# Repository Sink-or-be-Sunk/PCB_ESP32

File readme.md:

# Sink or be Sunk Hardware

This project contains the KiCAD PCB and auxiliary hardware needed for physical gameplay.

## Helpful Notes

### Nested Sheets

In KiCAD you can use a neat feature to split your project into multiple files. This not only helps to reduce cluter on one single diagram, it also allows for reuse of a common schematic element.

For this project specifically, the Grid.sch file can be reused for both the top (attack) grid and the bottom (ship positioning) grid.

`Hierarchical Labels` - KiCAD allows you to place a label on a nested sheet that can be viewed by the parenet sheet. Ex: you place a label on the STM32 Sheet and you can connect to it from the Main Layout schematic.

- Locate the `Hierarchical Labels` button on the right hand toolbar in kicad to place a label in a child sheet.
  - See section A4 of the STM32 Sheet
- Navigate back to the parent sheet and right click on the child sheet where you jused added the label
- Select the `import sheet pins` option
  - NOTE that you will have to do this for every new pin that you add to the child sheet, kinda repetative if you have a bunch of heirarchical labels...

`ESP32 Reference Design` - Adafruit produced a reference/dev board for the ESP32. They have great documentation on the device and are generous enough to include images of their schematic. This is a good place to start for our design. See the [Adafruit Website](https://learn.adafruit.com/adafruit-huzzah32-esp32-feather/downloads) for details.

#### PCB Updates to PCB_ESP32

I added a new branch with a new file "Main", containing all updated symbol and footprint libraries. There appears to be an issue between KiCad's footprint libraries in Version 4 and 5.0+. I believe I resolved this issue, let me know if you're still missing access to certain footprints. 

Other than that, I think this is a start. One great thing about our Main PCB is that the dimensions on it are much more flexible than the Row PCBs. If we need more room, we can make the board longer (wider will start to run into the grid). 

Some things to think about:
- USB to Serial: Where is the most convenient place for the plug? 
- What are the repercussions of placing the speaker next to the motor? 
- Where on the exterior of the board should the speaker knob/reset button go, without being bumped or in the way?

There's plenty of work left, but this is the start!

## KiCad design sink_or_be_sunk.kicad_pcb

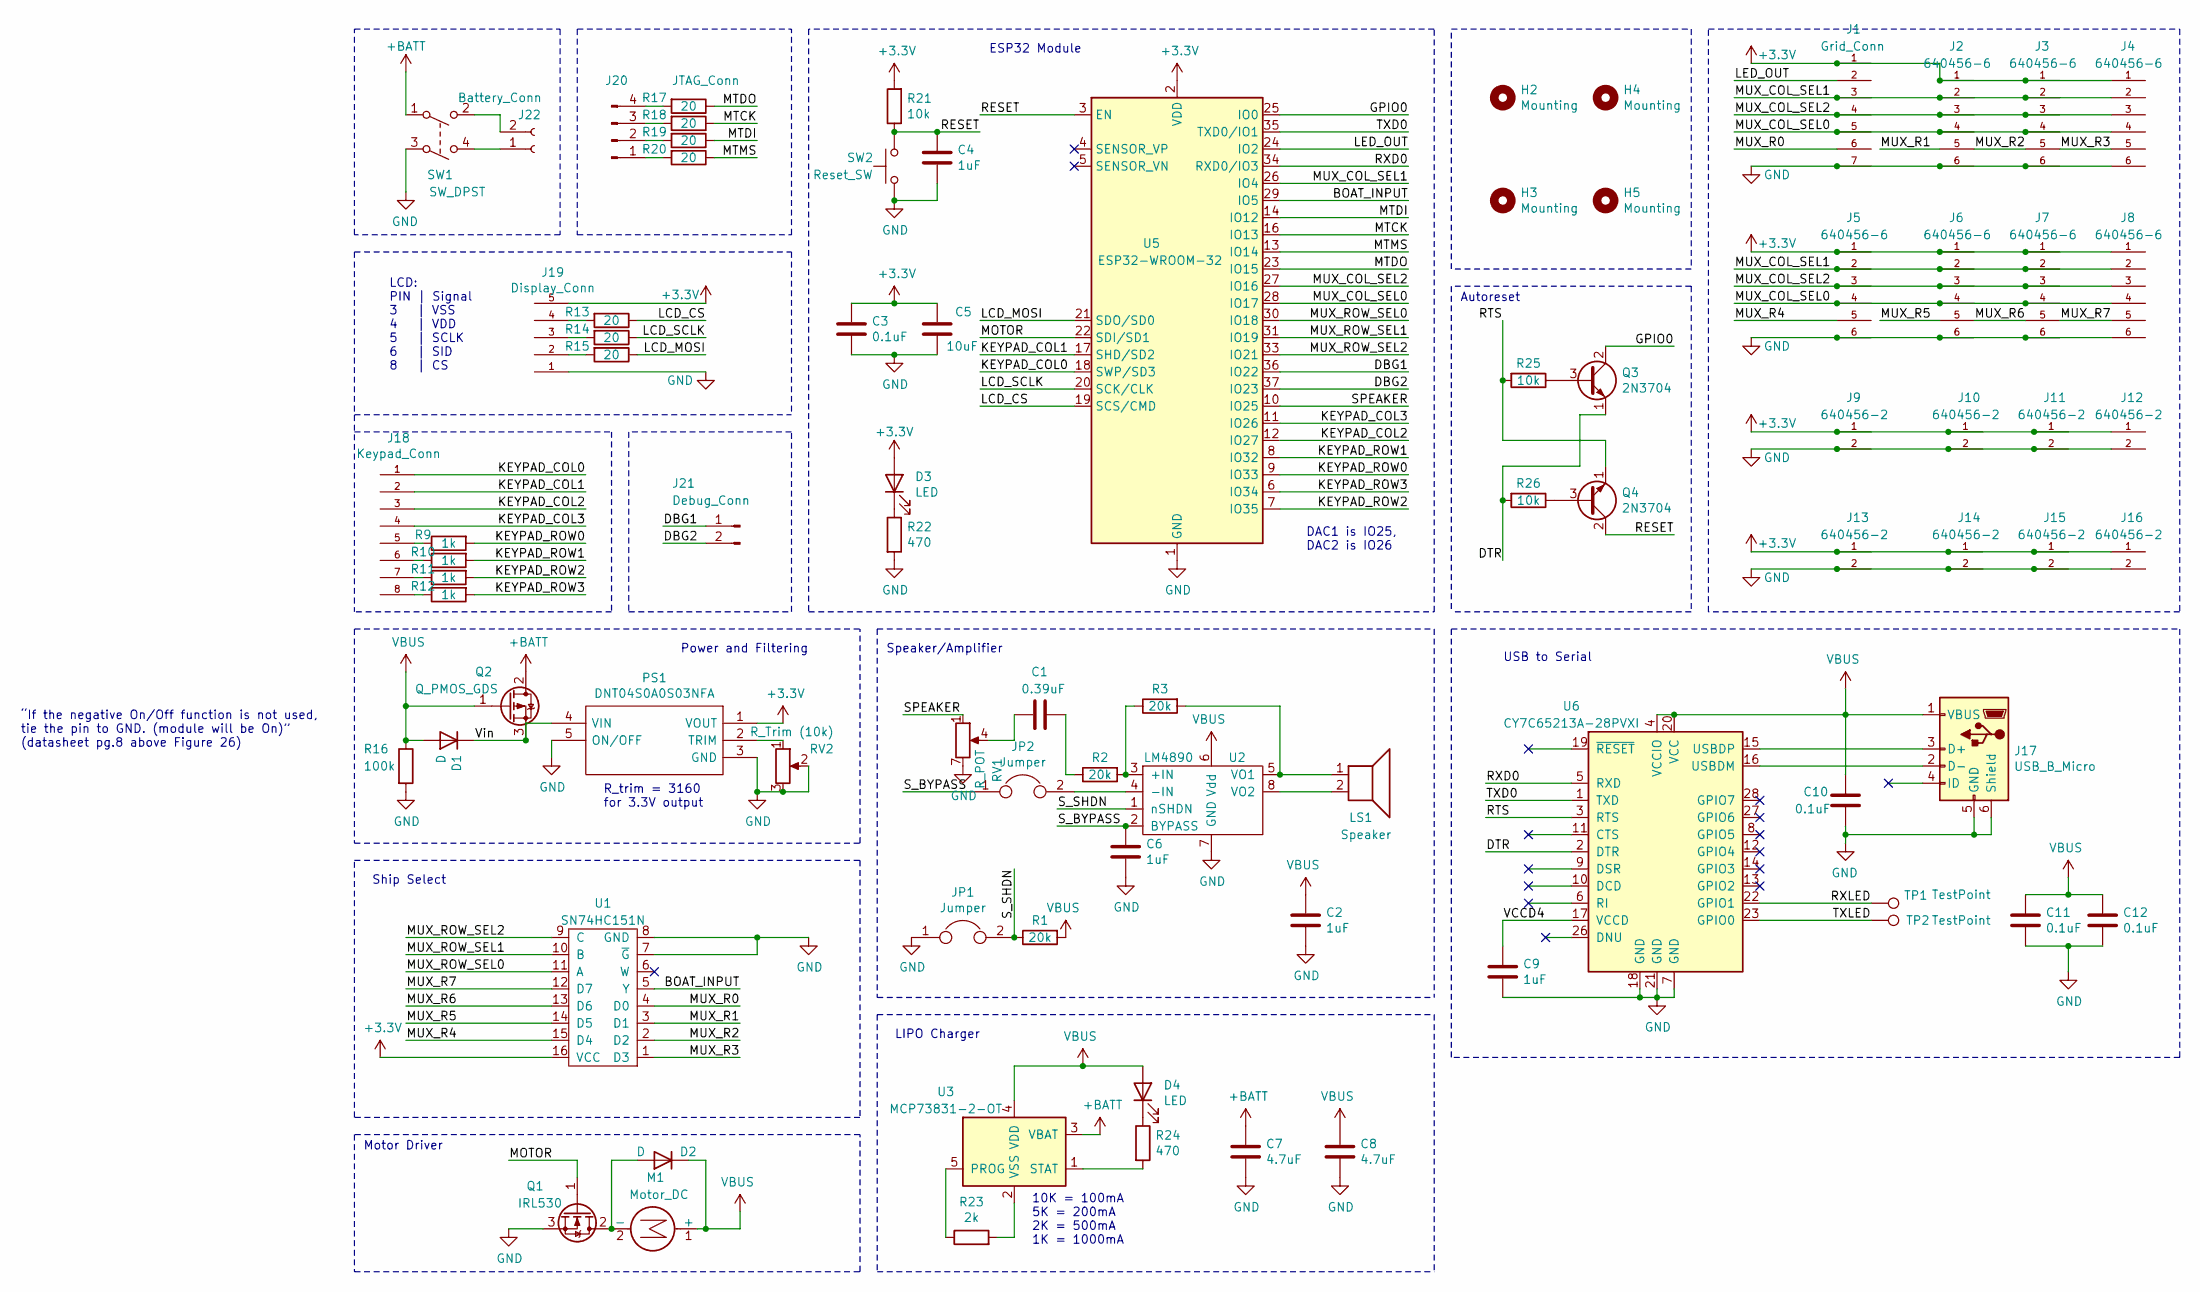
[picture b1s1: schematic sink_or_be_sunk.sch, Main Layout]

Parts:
C1: 0.39uF; C_0805_2012Metric_Pad1.18x1.45mm_HandSolder
C2, C4, C6: 1uF; C_0805_2012Metric_Pad1.18x1.45mm_HandSolder
C3, C10, C11, C12: 0.1uF; C_0805_2012Metric_Pad1.15x1.40mm_HandSolder
C5: 10uF; CP_Radial_D5.0mm_P2.50mm
C7, C8: 4.7uF; CP_Radial_D5.0mm_P2.50mm
C9: 1uF; C_0805_2012Metric_Pad1.15x1.40mm_HandSolder
D1, D2: D; D_A-405_P7.62mm_Horizontal
D3, D4: LED; LED_D3.0mm
H2, H3, H4, H5: Mounting; MountingHole_3.2mm_M3
J1: Grid_Conn; TE_640456-7
J2, J3, J4, J5, J6, J7, J8: 640456-6; TE_640456-6
J9, J10, J11, J12, J13, J14, J15, J16: 640456-2; TE_640456-2
J17: USB_B_Micro; USB_Micro_B_Female_Vert_1051330001
J18: Keypad_Conn; TE_640456-8
J19: Display_Conn; TE_640456-5
J20: JTAG_Conn; PinHeader_1x04_P2.54mm_Vertical
J21: Debug_Conn; PinHeader_1x02_P2.54mm_Vertical
J22: Battery_Conn; JST_PH_S2B-PH-K_1x02_P2.00mm_Horizontal
JP1, JP2: Jumper; PinHeader_1x02_P2.54mm_Vertical
LS1: Speaker; TE_640456-2
M1: Motor_DC; TE_640456-2
PS1: DNT04S0A0S03NFA; Mouser Part Number 108-DNT04S0A0S03NFA
Q1: IRL530; TO-220-3_Vertical
Q2: Q_PMOS_GDS; TO-251-3-1EP_Horizontal_TabDown
Q3, Q4: 2N3704; TO-92
R1, R2, R3: 20k; R_0805_2012Metric_Pad1.20x1.40mm_HandSolder
R9, R10, R11: 1k; R_0805_2012Metric_Pad1.20x1.40mm_HandSolder
R12: 1k; R_0805_2012Metric_Pad1.15x1.40mm_HandSolder
R13, R14, R15, R17, R18, R19, R20: 20; R_0805_2012Metric_Pad1.20x1.40mm_HandSolder
R16: 100k; R_0805_2012Metric_Pad1.15x1.40mm_HandSolder
R21, R25, R26: 10k; R_0805_2012Metric_Pad1.20x1.40mm_HandSolder
R22: 470; R_0805_2012Metric_Pad1.20x1.40mm_HandSolder
R23: 2k; R_0805_2012Metric_Pad1.15x1.40mm_HandSolder
R24: 470; R_0805_2012Metric_Pad1.15x1.40mm_HandSolder
RV1: R_POT; PinHeader_1x07_P2.54mm_Vertical
RV2: R_Trim (10k); Potentiometer_Bourns_3266Y_Vertical
SW1: SW_DPST; PinHeader_1x04_P2.54mm_Vertical
SW2: Reset_SW; PinHeader_1x02_P2.54mm_Vertical
TP1, TP2: TestPoint; TestPoint_Plated_Hole_D2.0mm
U1: SN74HC151N; DIP-16_W10.16mm
U2: LM4890; TSSOP-8_3x3mm_P0.65mm
U3: MCP73831-2-OT; SOT-23-5
U5: ESP32-WROOM-32
U6: CY7C65213A-28PVXI; SSOP-28_5.3x10.2mm_P0.65mm

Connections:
+3V3: C3.1, C5.1, D3.2 (A), J1.1, J2.1, J3.1, J4.1, J5.1, J6.1, J7.1, J8.1, J9.1, J10.1, J11.1, J12.1, J13.1, J14.1, J15.1, J16.1, J19.5, PS1.1 (VOUT), R21.2, U1.16 (VCC), U5.2 (VDD)
+BATT: C7.1, Q2.2 (D), SW1.1, U3.3 (VBAT)
/BOAT_INPUT: U1.5 (Y), U5.29 (IO5)
/DBG1: J21.1, U5.36 (IO22)
/DBG2: J21.2, U5.37 (IO23)
/DTR: Q3.1 (E), R26.2, U6.2 (DTR)
/GPIO0: Q3.2 (C), U5.25 (IO0)
/KEYPAD_COL0: J18.1, U5.18 (SWP/SD3)
/KEYPAD_COL1: J18.2, U5.17 (SHD/SD2)
/KEYPAD_COL2: J18.3, U5.12 (IO27)
/KEYPAD_COL3: J18.4, U5.11 (IO26)
/KEYPAD_ROW0: R9.2, U5.9 (IO33)
/KEYPAD_ROW1: R10.2, U5.8 (IO32)
/KEYPAD_ROW2: R11.2, U5.7 (IO35)
/KEYPAD_ROW3: R12.2, U5.6 (IO34)
/LCD_CS: R13.1, U5.19 (SCS/CMD)
/LCD_MOSI: R15.1, U5.21 (SDO/SD0)
/LCD_SCLK: R14.1, U5.20 (SCK/CLK)
/LED_OUT: J1.2, U5.24 (IO2)
/MOTOR: Q1.1 (G), U5.22 (SDI/SD1)
/MTCK: R18.1, U5.16 (IO13)
/MTDI: R19.1, U5.14 (IO12)
/MTDO: R17.1, U5.23 (IO15)
/MTMS: R20.1, U5.13 (IO14)
/MUX_COL_SEL0: J1.5, J2.4, J3.4, J4.4, J5.4, J6.4, J7.4, J8.4, U5.28 (IO17)
/MUX_COL_SEL1: J1.3, J2.2, J3.2, J4.2, J5.2, J6.2, J7.2, J8.2, U5.26 (IO4)
/MUX_COL_SEL2: J1.4, J2.3, J3.3, J4.3, J5.3, J6.3, J7.3, J8.3, U5.27 (IO16)
/MUX_R0: J1.6, U1.4 (D0)
/MUX_R1: J2.5, U1.3 (D1)
/MUX_R2: J3.5, U1.2 (D2)
/MUX_R3: J4.5, U1.1 (D3)
/MUX_R4: J5.5, U1.15 (D4)
/MUX_R5: J6.5, U1.14 (D5)
/MUX_R6: J7.5, U1.13 (D6)
/MUX_R7: J8.5, U1.12 (D7)
/MUX_ROW_SEL0: U1.11 (A), U5.30 (IO18)
/MUX_ROW_SEL1: U1.10 (B), U5.31 (IO19)
/MUX_ROW_SEL2: U1.9 (C), U5.33 (IO21)
/RESET: C4.1, Q4.2 (C), R21.1, SW2.2, U5.3 (EN)
/RTS: Q4.1 (E), R25.2, U6.3 (RTS)
/RXD0: U5.34 (RXD0/IO3), U6.5 (RXD)
/RXLED: TP1.1, U6.22 (GPIO1)
/SPEAKER: RV1.1, U5.10 (IO25)
/S_BYPASS: C6.1, JP2.1, U2.2 (BYPASS)
/S_SHDN: JP1.2, R1.1, U2.1 (nSHDN)
/TXD0: U5.35 (TXD0/IO1), U6.1 (TXD)
/TXLED: TP2.1, U6.23 (GPIO0)
/VCCD4: C9.1, U6.17 (VCCD)
/Vin: D1.1 (K), PS1.4 (VIN), Q2.3 (S)
GND: C2.2, C3.2, C4.2, C5.2, C6.2, C7.2, C8.2, C9.2, C10.2, C11.2, C12.2, J1.7, J2.6, J3.6, J4.6, J5.6, J6.6, J7.6, J8.6, J9.2, J10.2, J11.2, J12.2, J13.2, J14.2, J15.2, J16.2, J17.5 (GND), J17.6 (Shield), J19.1, JP1.1, PS1.3 (GND), PS1.5 (ON/OFF), Q1.3 (S), R16.2, R22.2, RV1.7, RV2.2, RV2.3, SW1.3, SW2.1, U1.7 (~G), U1.8 (GND), U2.7 (GND), U5.1 (GND), U5.15 (GND), U5.38 (GND), U5.39 (GND), U6.7 (GND), U6.18 (GND), U6.21 (GND)
unnamed: C1.1, RV1.4
unnamed: C1.2, R2.1
unnamed: D2.2 (A), M1.2 (-), Q1.2 (D)
unnamed: D3.1 (K), R22.1
unnamed: D4.1 (K), R24.1
unnamed: J17.2 (D-), U6.16 (USBDM)
unnamed: J17.3 (D+), U6.15 (USBDP)
unnamed: J18.5, R9.1
unnamed: J18.6, R10.1
unnamed: J18.7, R11.1
unnamed: J18.8, R12.1
unnamed: J19.2, R15.2
unnamed: J19.3, R14.2
unnamed: J19.4, R13.2
unnamed: J20.1, R20.2
unnamed: J20.2, R19.2
unnamed: J20.3, R18.2
unnamed: J20.4, R17.2
unnamed: J22.1, SW1.4
unnamed: J22.2, SW1.2
unnamed: JP2.2, U2.4 (-IN)
unnamed: LS1.1, R3.2, U2.5 (VO1)
unnamed: LS1.2, U2.8 (VO2)
unnamed: PS1.2 (TRIM), RV2.1
unnamed: Q3.3 (B), R25.1
unnamed: Q4.3 (B), R26.1
unnamed: R2.2, R3.1, U2.3 (+IN)
unnamed: R23.1, U3.5 (PROG)
unnamed: R23.2, U3.2 (VSS)
unnamed: R24.2, U3.1 (STAT)
VBUS: C2.1, C8.1, C10.1, C11.1, C12.1, D1.2 (A), D2.1 (K), D4.2 (A), J17.1 (VBUS), M1.1 (+), Q2.1 (G), R1.2, R16.1, U2.6 (Vdd), U3.4 (VDD), U6.4 (VCCIO), U6.20 (VCC)

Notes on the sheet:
LCD: PIN | Signal 3 | VSS 4 | VDD 5 | SCLK 6 | SID 8 | CS
10K = 100mA 5K = 200mA 2K = 500mA 1K = 1000mA
USB to Serial
ESP32 Module
Motor Driver
Autoreset
LIPO Charger
Ship Select
Speaker/Amplifier
DAC1 is IO25, DAC2 is IO26
“If the negative On/Off function is not used, tie the pin to GND. (module will be On)” (datasheet pg.8 above Figure 26)
R_trim = 3160 for 3.3V output
Power and Filtering

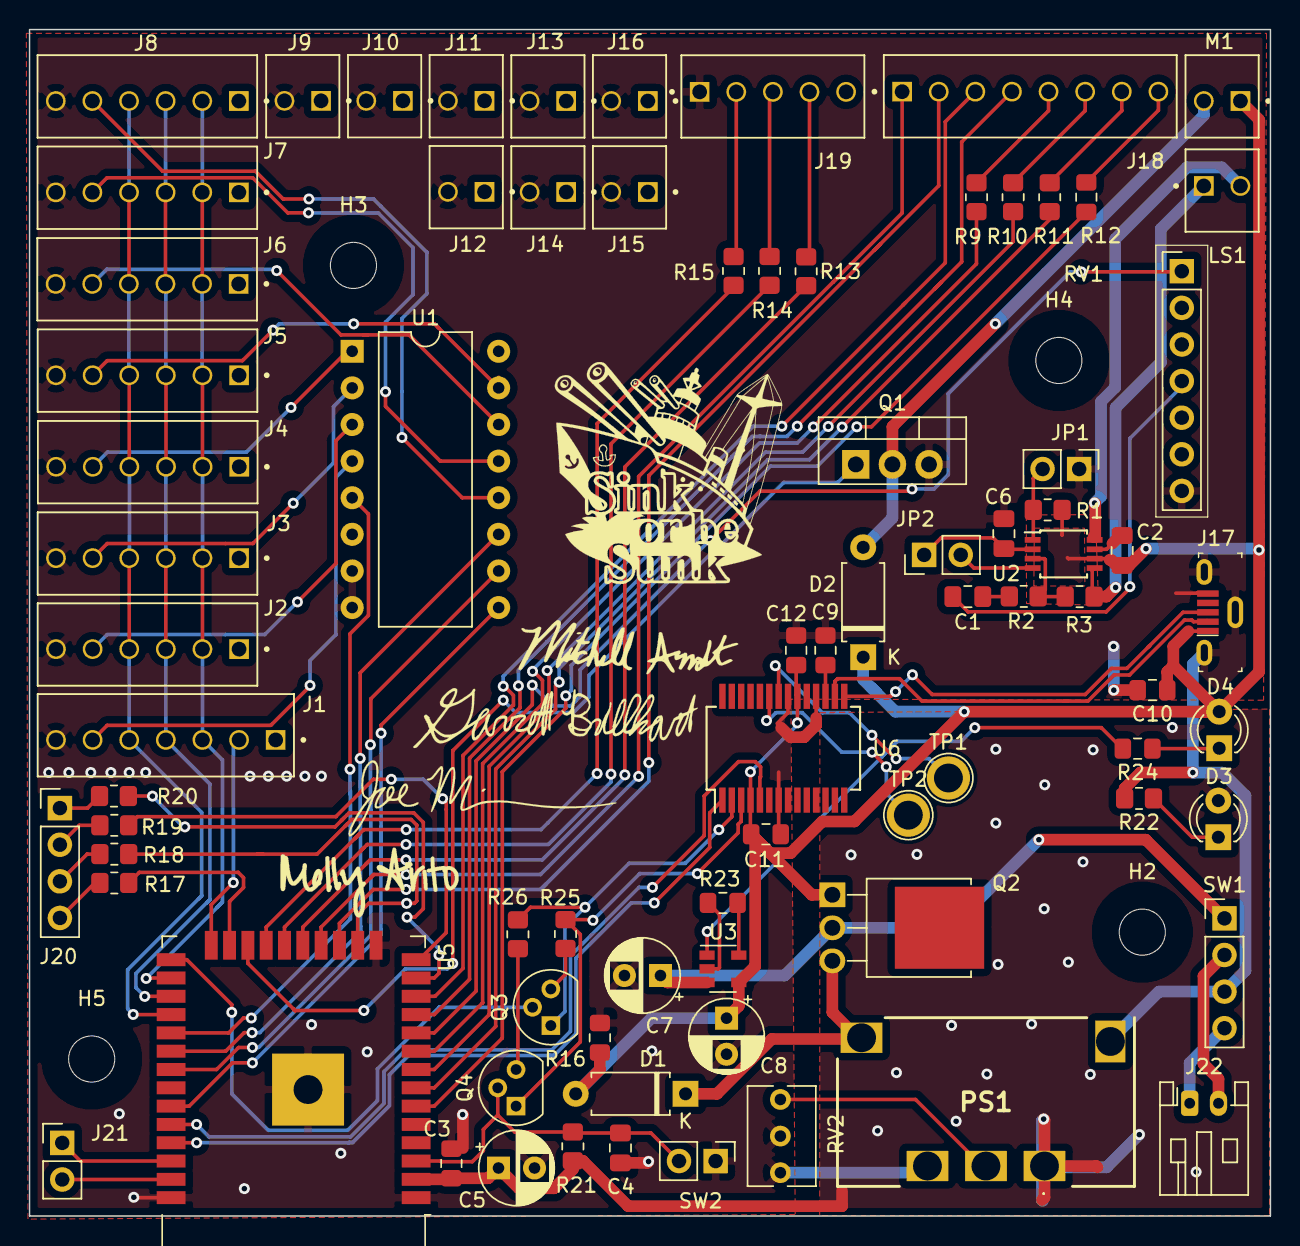
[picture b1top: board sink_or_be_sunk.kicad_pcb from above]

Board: 2 copper layers, 86.1 x 82.3 mm, 83 parts (0 on the bottom side), 81 nets.

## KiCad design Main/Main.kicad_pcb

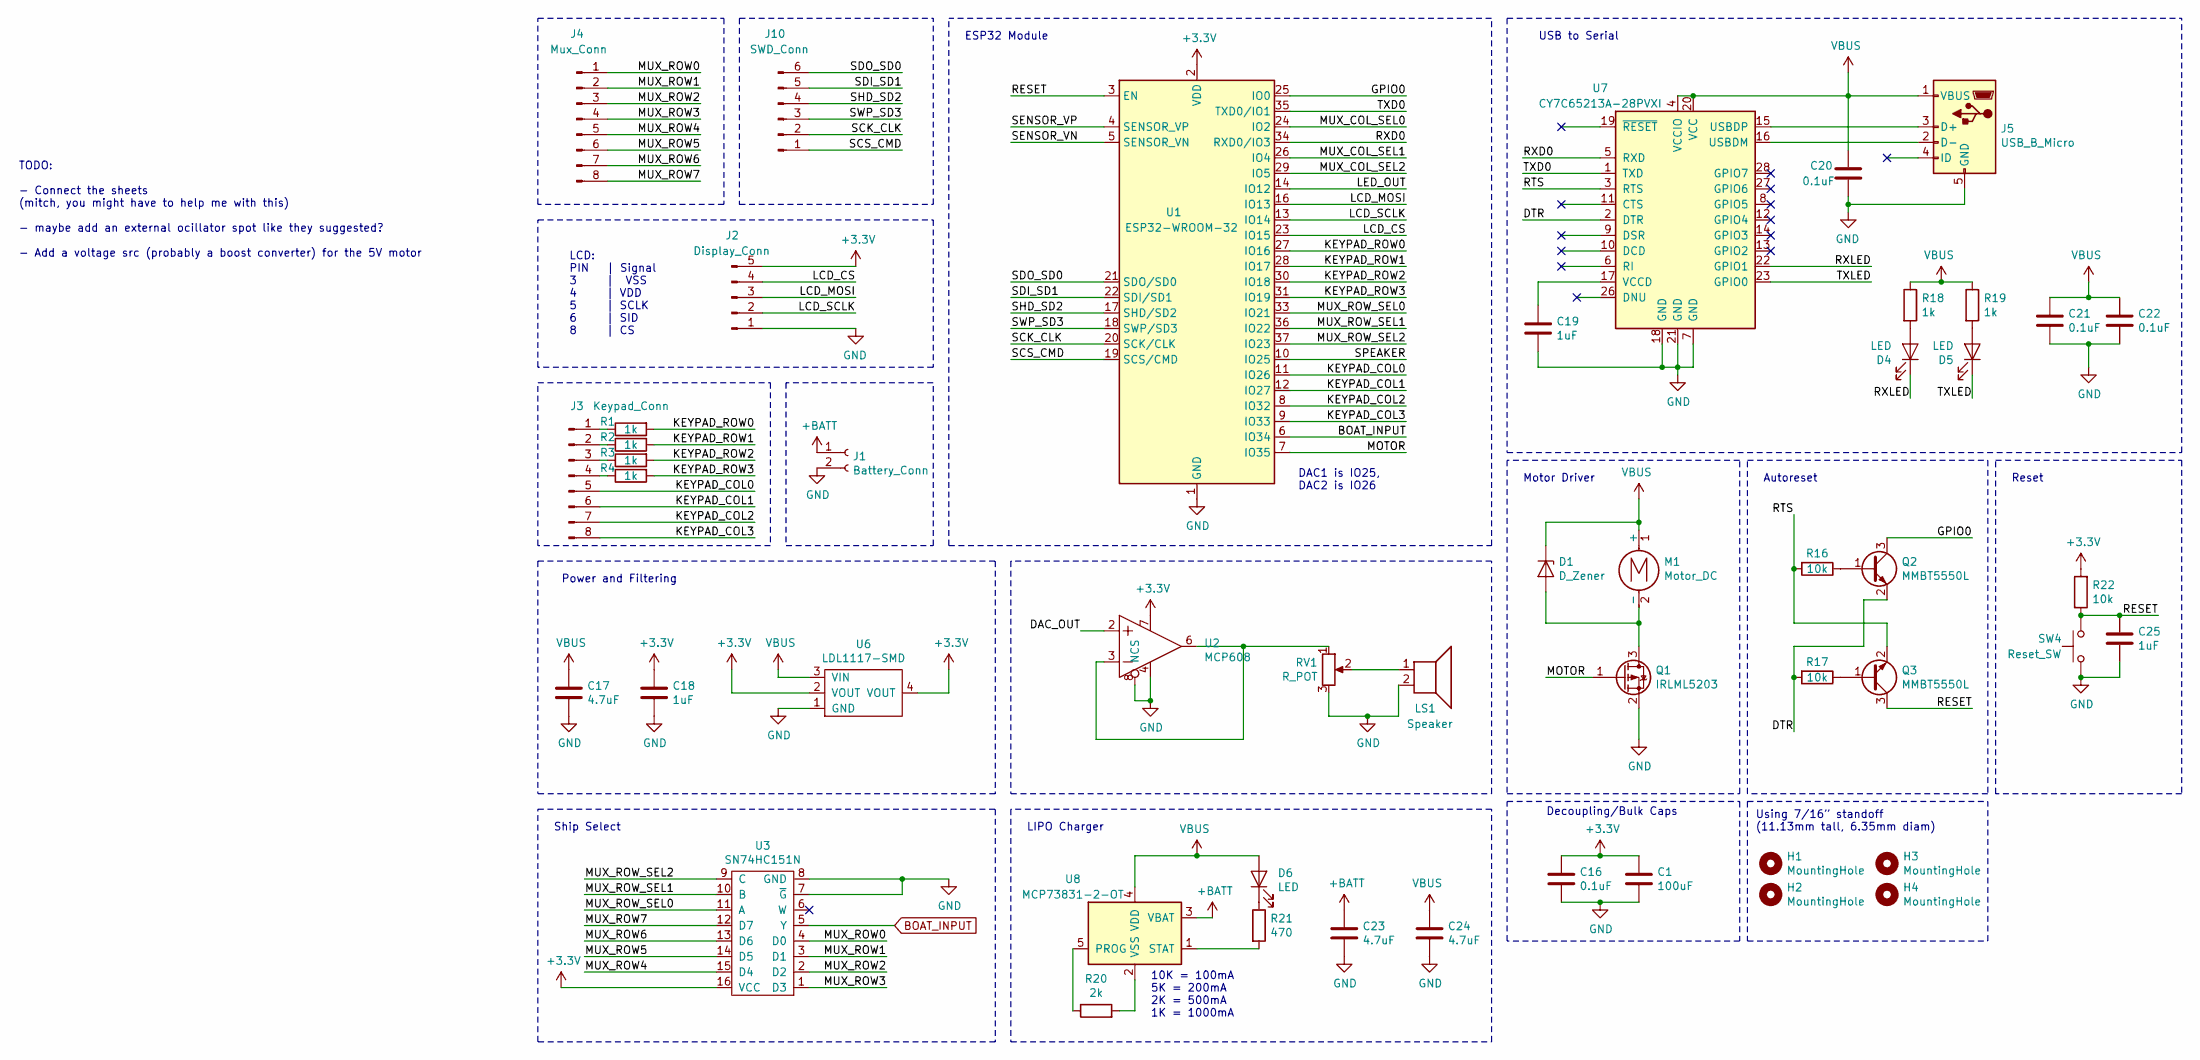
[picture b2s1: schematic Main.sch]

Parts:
C1: 100uF; C_0805_2012Metric_Pad1.15x1.40mm_HandSolder
C16, C20, C21, C22: 0.1uF; C_0805_2012Metric_Pad1.15x1.40mm_HandSolder
C17, C23, C24: 4.7uF; C_0805_2012Metric_Pad1.15x1.40mm_HandSolder
C18, C19, C25: 1uF; C_0805_2012Metric_Pad1.15x1.40mm_HandSolder
D1: D_Zener; D_0805_2012Metric_Pad1.15x1.40mm_HandSolder
D4, D5, D6: LED; LED_D3.0mm
H1, H2, H3, H4: MountingHole; MountingHole_6.4mm_M6
J1: Battery_Conn; JST_PH_S2B-PH-K_1x02_P2.00mm_Horizontal
J2: Display_Conn; PinHeader_1x05_P2.54mm_Horizontal
J3: Keypad_Conn; PinSocket_1x08_P2.54mm_Vertical
J4: Mux_Conn; PinHeader_1x08_P2.54mm_Vertical
J5: USB_B_Micro; USB_Micro_B_Female_Vert_1051330001
J10: SWD_Conn; PinHeader_1x06_P2.54mm_Vertical
LS1: Speaker; PinHeader_1x02_P2.54mm_Horizontal
M1: Motor_DC; PinHeader_1x02_P2.54mm_Vertical
Q1: IRLML5203; SOT-23
Q2, Q3: MMBT5550L; SOT-23
R1, R2, R3, R4, R18, R19: 1k; R_0805_2012Metric_Pad1.15x1.40mm_HandSolder
R16, R17, R22: 10k; R_0805_2012Metric_Pad1.15x1.40mm_HandSolder
R20: 2k; R_0805_2012Metric_Pad1.15x1.40mm_HandSolder
R21: 470; R_0805_2012Metric_Pad1.15x1.40mm_HandSolder
RV1: R_POT; PinHeader_1x03_P2.54mm_Horizontal
SW4: Reset_SW; PinHeader_1x02_P2.54mm_Horizontal
U1: ESP32-WROOM-32
U2: MCP608; DIP-8_W7.62mm
U3: SN74HC151N; SN74HC151N-PDIP
U6: LDL1117-SMD; SOT-223
U7: CY7C65213A-28PVXI; SSOP-28_5.3x10.2mm_P0.65mm
U8: MCP73831-2-OT; SOT-23-5

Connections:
+3V3: C1.1, C16.1, C18.1, J2.5, R22.2, U1.2 (VDD), U2.7, U3.16 (VCC), U6.2 (VOUT), U6.4 (VOUT)
+BATT: C23.1, J1.1, U8.3 (VBAT)
/DAC_OUT: U2.2
/DTR: Q2.2 (E), R17.2, U7.2 (DTR)
/GPIO0: Q2.3 (C), U1.25 (IO0)
/KEYPAD_COL0: J3.5, U1.11 (IO26)
/KEYPAD_COL1: J3.6, U1.12 (IO27)
/KEYPAD_COL2: J3.7, U1.8 (IO32)
/KEYPAD_COL3: J3.8, U1.9 (IO33)
/KEYPAD_ROW0: R1.2, U1.27 (IO16)
/KEYPAD_ROW1: R2.2, U1.28 (IO17)
/KEYPAD_ROW2: R3.2, U1.30 (IO18)
/KEYPAD_ROW3: R4.2, U1.31 (IO19)
/LCD_CS: J2.4, U1.23 (IO15)
/LCD_MOSI: J2.3, U1.16 (IO13)
/LCD_SCLK: J2.2, U1.13 (IO14)
/LED_OUT: U1.14 (IO12)
/MOTOR: Q1.1 (G), U1.7 (IO35)
/MUX_COL_SEL0: U1.24 (IO2)
/MUX_COL_SEL1: U1.26 (IO4)
/MUX_COL_SEL2: U1.29 (IO5)
/MUX_ROW0: J4.1, U3.4 (D0)
/MUX_ROW1: J4.2, U3.3 (D1)
/MUX_ROW2: J4.3, U3.2 (D2)
/MUX_ROW3: J4.4, U3.1 (D3)
/MUX_ROW4: J4.5, U3.15 (D4)
/MUX_ROW5: J4.6, U3.14 (D5)
/MUX_ROW6: J4.7, U3.13 (D6)
/MUX_ROW7: J4.8, U3.12 (D7)
/MUX_ROW_SEL0: U1.33 (IO21), U3.11 (A)
/MUX_ROW_SEL1: U1.36 (IO22), U3.10 (B)
/MUX_ROW_SEL2: U1.37 (IO23), U3.9 (C)
/RESET: C25.1, Q3.3 (C), R22.1, SW4.2, U1.3 (EN)
/RTS: Q3.2 (E), R16.2, U7.3 (RTS)
/RXD0: U1.34 (RXD0/IO3), U7.5 (RXD)
/RXLED: D4.1 (K), U7.22 (GPIO1)
/SCK_CLK: J10.2, U1.20 (SCK/CLK)
/SCS_CMD: J10.1, U1.19 (SCS/CMD)
/SDI_SD1: J10.5, U1.22 (SDI/SD1)
/SDO_SD0: J10.6, U1.21 (SDO/SD0)
/SENSOR_VN: U1.5 (SENSOR_VN)
/SENSOR_VP: U1.4 (SENSOR_VP)
/SHD_SD2: J10.4, U1.17 (SHD/SD2)
/SPEAKER: U1.10 (IO25)
/SWP_SD3: J10.3, U1.18 (SWP/SD3)
/TXD0: U1.35 (TXD0/IO1), U7.1 (TXD)
/TXLED: D5.1 (K), U7.23 (GPIO0)
BOAT_INPUT: U1.6 (IO34), U3.5 (Y)
GND: C1.2, C16.2, C17.2, C18.2, C19.2, C20.2, C21.2, C22.2, C23.2, C24.2, C25.2, J1.2, J2.1, J5.5 (GND), LS1.2, Q1.2 (S), RV1.3, SW4.1, U1.1 (GND), U1.15 (GND), U1.38 (GND), U1.39 (GND), U2.4, U2.8 (NCS), U3.7 (~G), U3.8 (GND), U6.1 (GND), U7.7 (GND), U7.18 (GND), U7.21 (GND)
unnamed: C19.1, U7.17 (VCCD)
unnamed: D1.2 (A), M1.2 (-), Q1.3 (D)
unnamed: D4.2 (A), R18.2
unnamed: D5.2 (A), R19.2
unnamed: D6.1 (K), R21.1
unnamed: J3.1, R1.1
unnamed: J3.2, R2.1
unnamed: J3.3, R3.1
unnamed: J3.4, R4.1
unnamed: J5.2 (D-), U7.16 (USBDM)
unnamed: J5.3 (D+), U7.15 (USBDP)
unnamed: LS1.1, RV1.2
unnamed: Q2.1 (B), R16.1
unnamed: Q3.1 (B), R17.1
unnamed: R20.1, U8.5 (PROG)
unnamed: R20.2, U8.2 (VSS)
unnamed: R21.2, U8.1 (STAT)
unnamed: RV1.1, U2.3, U2.6
VBUS: C17.1, C20.1, C21.1, C22.1, C24.1, D1.1 (K), D6.2 (A), J5.1 (VBUS), M1.1 (+), R18.1, R19.1, U6.3 (VIN), U7.4 (VCCIO), U7.20 (VCC), U8.4 (VDD)

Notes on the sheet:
TODO: - Connect the sheets (mitch, you might have to help me with this) - maybe add an external ocillator spot like they suggested? - Add a voltage src (probably a boost converter) for the 5V motor
LCD: PIN | Signal 3 | VSS 4 | VDD 5 | SCLK 6 | SID 8 | CS
DAC1 is IO25, DAC2 is IO26
Decoupling/Bulk Caps
10K = 100mA 5K = 200mA 2K = 500mA 1K = 1000mA
Using 7/16” standoff (11.13mm tall, 6.35mm diam)
USB to Serial
ESP32 Module
Motor Driver
Autoreset
Reset
LIPO Charger
Ship Select
Power and Filtering

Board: 2 copper layers, 49 parts (0 on the bottom side), 60 nets, no tracks yet.

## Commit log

2021-09-01 imported ece 362 project and added template for main schematic
2021-09-01 updated the readme and added example of heirarchical labels
2021-09-01 addes esp32 info to readme
2021-09-17 removed unneeded sheets and added speaker sheet/circuit
2021-09-22 added all pin definitions
2021-09-30 first iteration of main pcb
2021-09-30 cleaned up files
2021-09-30 check speaker pot footprint
2021-09-30 added some notes/todos on schematic
2021-10-01 updated todo
2021-10-01 made some tweaks to usb/power circuits
2021-10-01 ready to put on homepage
2021-10-03 updated serial programming circuitry
2021-10-03 updated todos with 5V motor requirement
2021-10-06 Check Main for PCB updates
2021-10-06 Continued progress
2021-10-06 cleaned up project
2021-10-06 added electrical isoltion switch
2021-10-06 redo of layout and minor circuit updates
2021-10-07 minor updates to board settings
2021-10-07 10/7 organizing ratsnest more
2021-10-07 updated with todos from talk with prof
2021-10-08 finished routing power and programming circuit
2021-10-08 before pin shift
2021-10-08 finsihed routing mux
2021-10-08 fixed error in grid conn sch
2021-10-08 all components placed, need to finish up the routing
2021-10-08 finished layout, some drc errors that need fixing
2021-10-08 added edge cuts
2021-10-08 ignore
2021-10-09 connector updates
2021-10-09 mitch-local
2021-10-09 left off shrinking width
2021-10-10 finsihed 79x85mm layout
2021-10-10 added some notes/questions to sch/pcb
2021-10-13 added new switching regulator footprint
2021-10-13 before switching pmos
2021-10-13 updated switching regulator and pmos
2021-10-13 added logo to board
2021-10-14 added team signatures to the board
2021-10-14 updated trace widths
2021-10-14 updated edge cuts
2021-10-14 updated back copper to power plane
2021-10-15 added new connectors
2021-10-15 cleaned up footprints
2021-10-15 updated library with footprints
2021-10-15 brought over board from regulator
2021-10-15 updated with new regulator symbol
2021-10-15 brought over regulator footprint
2021-10-15 merged connectors and regulator footprint
2021-10-16 updated dimensions
2021-10-18 fixed issue with attack connector labels
2021-10-19 updated hole footprint, power plane adjustments
2021-10-21 left off working on amp
2021-10-21 updated schematic for new amp
2021-10-21 finished merge with amp
2021-10-21 finished routing with new circuit and added back silk screen
2021-10-21 updated silkscreen refs for new amp circuit
